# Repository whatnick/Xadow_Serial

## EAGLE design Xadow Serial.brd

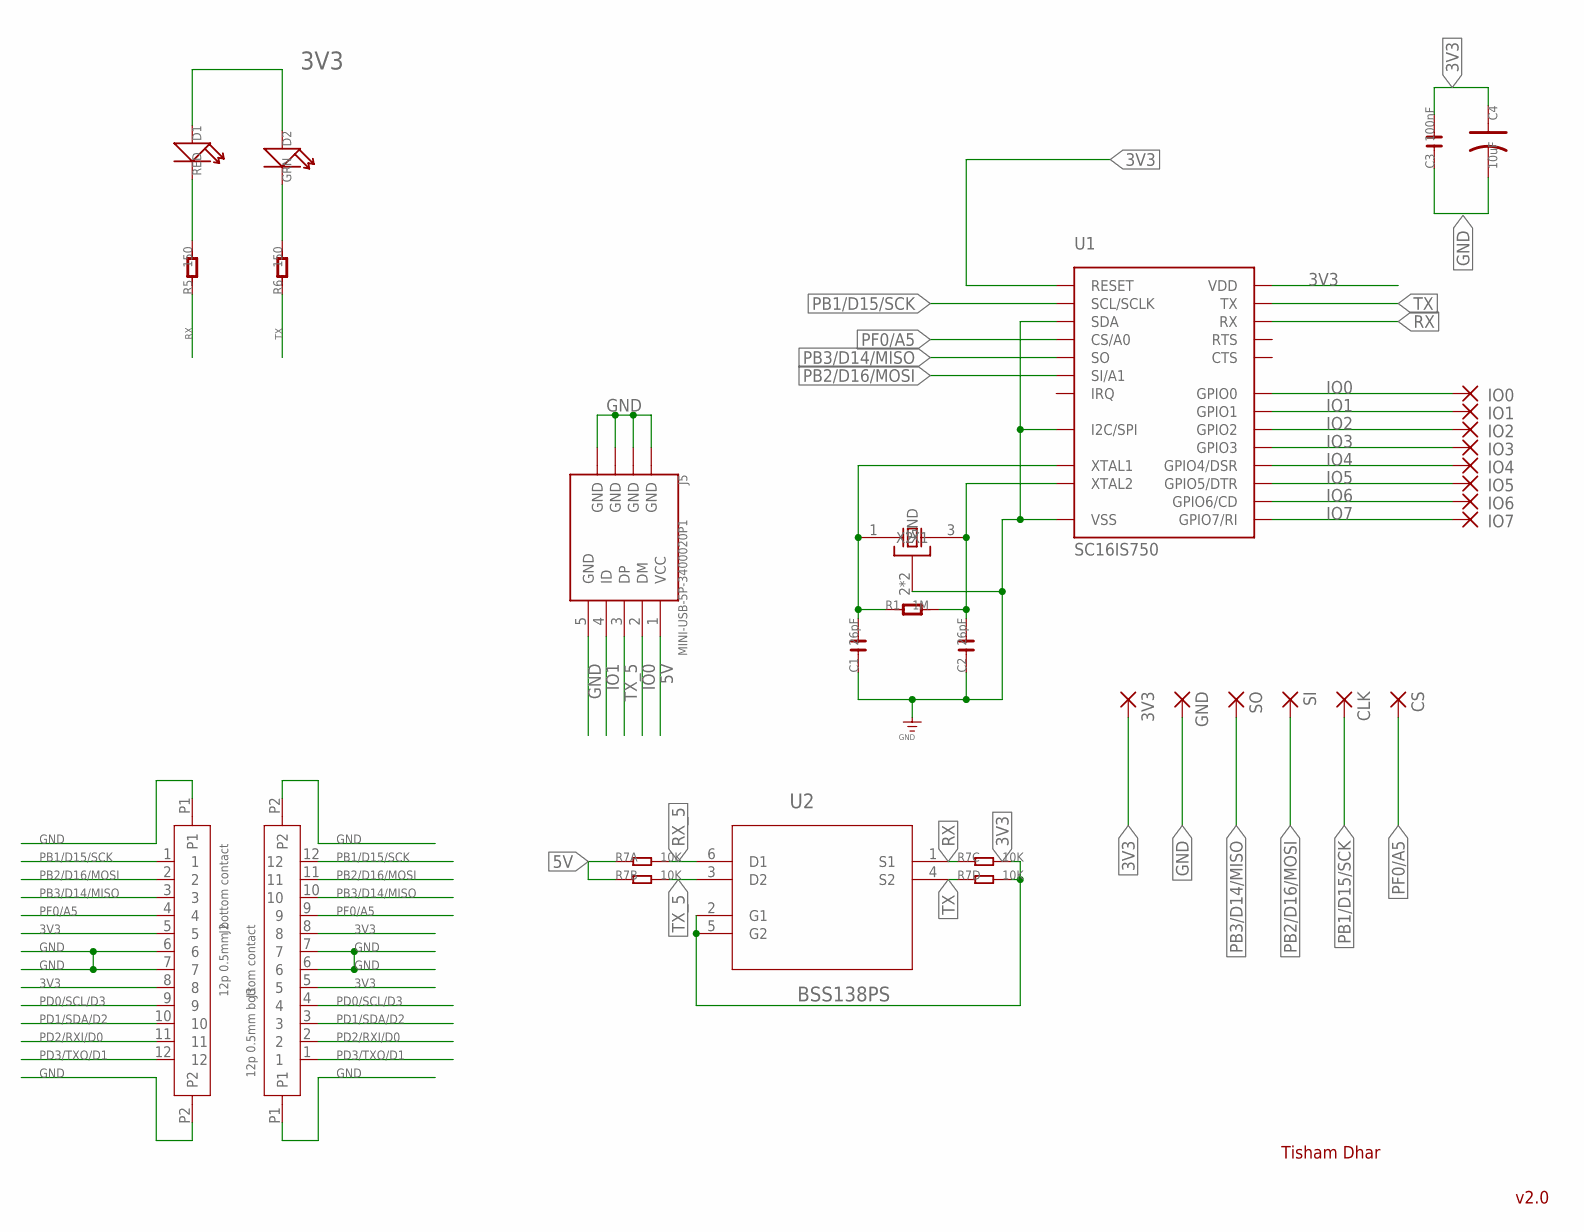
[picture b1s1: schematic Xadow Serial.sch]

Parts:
3V3: WIREPADSMD1,27-254; SMD1,27-2,54
C1, C2: 26pF; C0603
C3: 100nF; C0603
C4: 10uF; AVX-A
CLK: WIREPADSMD1,27-254; SMD1,27-2,54
CS: WIREPADSMD1,27-254; SMD1,27-2,54
D1: RED; LED0603
D2: GRN; LED0603
GND: WIREPADSMD1,27-254; SMD1,27-2,54
IO0, IO1, IO2, IO3, IO4, IO5, IO6, IO7: WIREPADSMD1,27-254; SMD1,27-2,54
J2, J3: 12p 0.5mm bottom contact; 12P-0.5
J5: MINI-USB-5P-3400020P1; MINI-B-SMD
R1: 1M; R0603
R5, R6: 150; R0603
R7: 10K; 1206-8-3.3X2.4
SI: WIREPADSMD1,27-254; SMD1,27-2,54
SO: WIREPADSMD1,27-254; SMD1,27-2,54
U1: SC16IS750; TSSOP_24
U2: BSS138PS; SOT65P210X110-6N
X1: CTS_32X25_SMD; CTS_32X25

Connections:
3V3: 3V3.1, C3.2, C4.+ (1), D1.+, D2.+, J2.5, J2.8, J3.5, J3.8, R7.5 (2), R7.6 (2), U1.P$4 (RESET), U1.P$7 (VDD), U2.2 (G1), U2.5 (G2)
5V: J5.1 (VCC), R7.1, R7.2 (1)
GND: C1.1, C2.1, C3.1, C4.- (2), GND.1, J2.6, J2.7, J2.P1, J2.P2, J3.6, J3.7, J3.P1, J3.P2, J5.5 (GND), J5.P$1 (GND), J5.P$2 (GND), J5.P$3 (GND), J5.P$4 (GND), U1.P$8 (I2C/SPI), U1.P$13 (SDA), U1.P$19 (VSS), X1.2 (GND), X1.4 (GND)
IO0: IO0.1, J5.2 (DM), U1.P$15 (GPIO0)
IO1: IO1.1, J5.4 (ID), U1.P$16 (GPIO1)
IO2: IO2.1, U1.P$17 (GPIO2)
IO3: IO3.1, U1.P$18 (GPIO3)
IO4: IO4.1, U1.P$20 (GPIO4/DSR)
IO5: IO5.1, U1.P$21 (GPIO5/DTR)
IO6: IO6.1, U1.P$22 (GPIO6/CD)
IO7: IO7.1, U1.P$23 (GPIO7/RI)
unnamed: C1.2, R1.1, U1.P$5 (XTAL1), X1.1 (X1)
unnamed: C2.2, R1.2, U1.P$6 (XTAL2), X1.3 (X2)
unnamed: D1.-, R5.2
unnamed: D2.-, R6.2
PB1/D15/SCK: CLK.1, J2.1, J3.12, U1.P$12 (SCL/SCLK)
PB2/D16/MOSI: J2.2, J3.11, SI.1, U1.P$10 (SI/A1)
PB3/D14/MISO: J2.3, J3.10, SO.1, U1.P$11 (SO)
PD0/SCL/D3: J2.9, J3.4
PD1/SDA/D2: J2.10, J3.3
PD2/RXI/D0: J2.11, J3.2
PD3/TXO/D1: J2.12, J3.1
PF0/A5: CS.1, J2.4, J3.9, U1.P$9 (CS/A0)
RX: R5.1, R7.3 (1), U1.P$3 (RX), U2.1 (S1)
RX_5: R7.8 (2), U2.6 (D1)
TX: R6.1, R7.4 (1), U1.P$2 (TX), U2.4 (S2)
TX_5: J5.3 (DP), R7.7 (2), U2.3 (D2)

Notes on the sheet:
Tisham Dhar
v2.0

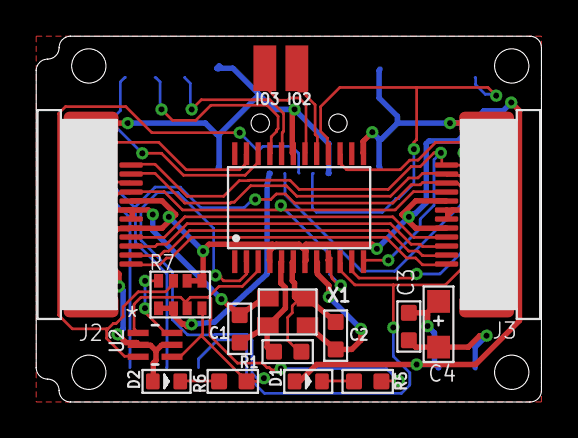
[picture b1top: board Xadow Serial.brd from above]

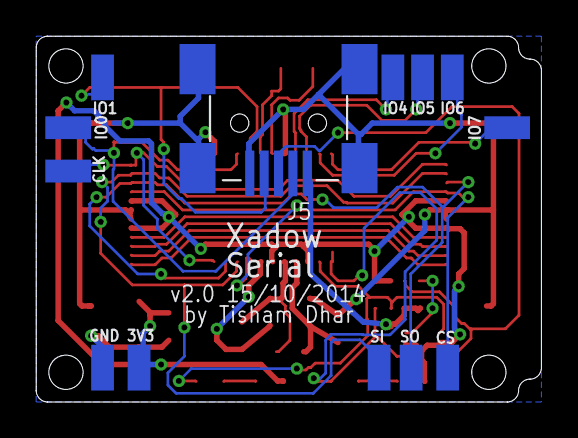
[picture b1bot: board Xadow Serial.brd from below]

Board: 2 copper layers, 28.1 x 20.3 mm, 30 parts (13 on the bottom side), 27 nets.

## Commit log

2014-10-18 Initial import
2014-10-19 Fully routed with solder jumpers
2014-10-19 Fixed up labels
2014-10-20 Change labels for visibility
2014-10-20 Create tented vias
2014-10-20 Moved solder jumpers to the bottom
2014-10-20 Topside silk screen
2014-10-20 Lettering size
2014-10-21 Switched to cheaper QFN package
2015-01-27 Better crystal location
2015-01-27 Some more component position fiddling
2015-01-28 Routed to OSHPark DRU and sent for fab
2015-02-07 Converted to use SPI
2015-02-07 Finished routing in SPI mode
